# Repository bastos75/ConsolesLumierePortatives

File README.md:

# ConsolesLumierePortatives
Consoles lumière pour spectacle de parade -- connectées par modules MeshBee de Seeedstudio

2 types de console : 
  - la complète avec 4 sorties + telecommande connectable.
  - la réduite avec 1 sortie
  
Les boîtiers sont à imprimer en 3D

Un module de création et de gestion des mémoires lumière est programmé en Processing

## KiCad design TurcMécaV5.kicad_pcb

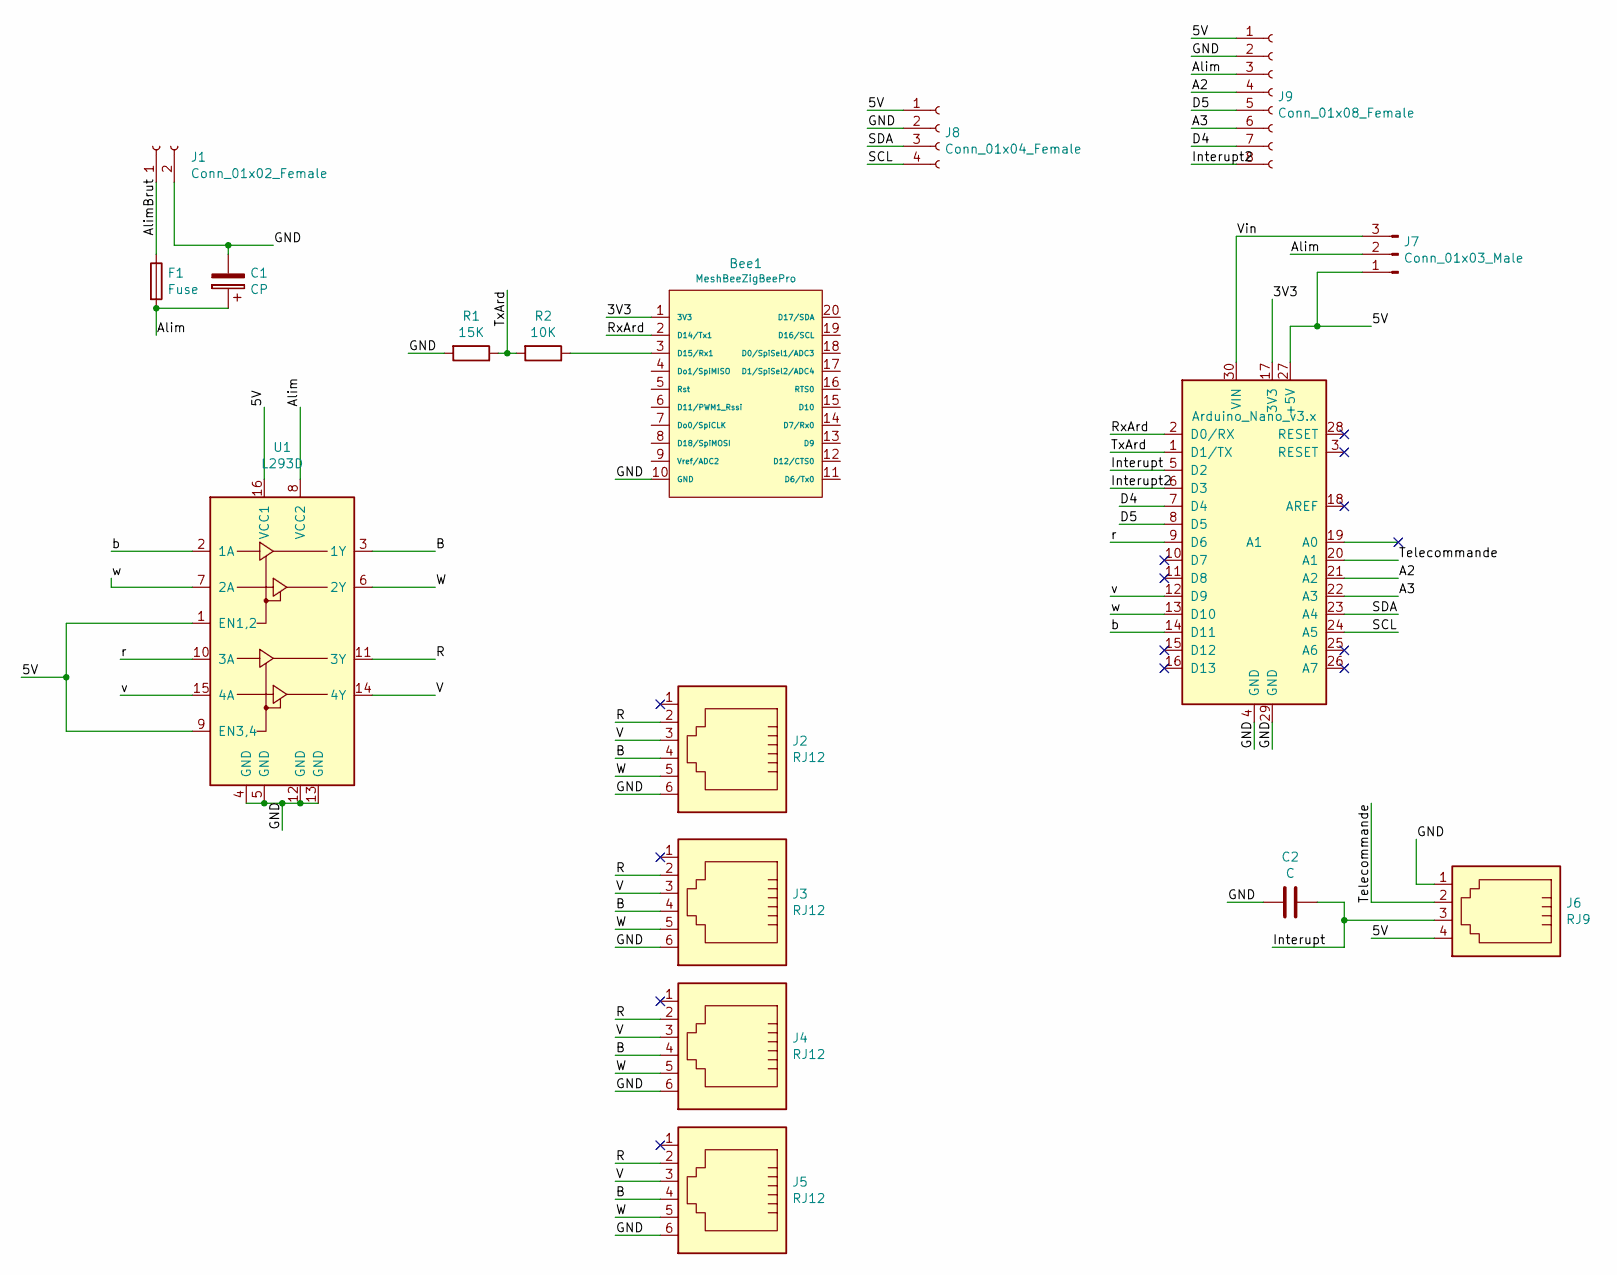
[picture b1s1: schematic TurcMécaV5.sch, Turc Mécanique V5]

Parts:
A1: Arduino_Nano_v3.x; Arduino_NanoPersonnalisé
Bee1: MeshBeeZigBeePro
C1: CP; CP_Radial_D5.0mm_P2.50mm
C2: C; C_Disc_D3.0mm_W1.6mm_P2.50mm
F1: Fuse; Fusible_Fuse_Perso
J1: Conn_01x02_Female; PinHeader_1x02_P2.54mm_Vertical
J2, J3, J4, J5: RJ12; RJ12_Amphenol_54601
J6: RJ9; RJ9_Amphenol_personnalisé
J7: Conn_01x03_Male; FanPinHeader_1x03_P2.54mm_Vertical
J8: Conn_01x04_Female; PinHeader_1x04_P2.54mm_Vertical
J9: Conn_01x08_Female; PinHeader_2x04_P2.54mm_Vertical
R1: 15K; R_Axial_DIN0411_L9.9mm_D3.6mm_P12.70mm_Horizontal
R2: 10K; R_Axial_DIN0411_L9.9mm_D3.6mm_P12.70mm_Horizontal
U1: L293D; DIP-16_W7.62mm_LongPads

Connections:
/3V3: A1.17 (3V3), Bee1.1 (3V3)
/5V: A1.27 (+5V), J6.4, J7.1, J8.1, J9.1, U1.1 (EN1,2), U1.9 (EN3,4), U1.16 (VCC1)
/A2: A1.21 (A2), J9.4
/A3: A1.22 (A3), J9.6
/Alim: C1.1, F1.2, J7.2, J9.3, U1.8 (VCC2)
/AlimBrut: F1.1, J1.1
/B: J2.4, J3.4, J4.4, J5.4, U1.3 (1Y)
/D4: A1.7 (D4), J9.7
/D5: A1.8 (D5), J9.5
/GND: A1.4 (GND), A1.29 (GND), Bee1.10 (GND), C1.2, C2.2, J1.2, J2.6, J3.6, J4.6, J5.6, J6.1, J8.2, J9.2, R1.2, U1.4 (GND), U1.5 (GND), U1.12 (GND), U1.13 (GND)
/Interupt: A1.5 (D2), C2.1, J6.3
/Interupt2: A1.6 (D3), J9.8
/R: J2.2, J3.2, J4.2, J5.2, U1.11 (3Y)
/RxArd: A1.2 (D0/RX), Bee1.2 (D14/Tx1)
/SCL: A1.24 (A5), J8.4
/SDA: A1.23 (A4), J8.3
/Telecommande: A1.20 (A1), J6.2
/TxArd: A1.1 (D1/TX), R1.1, R2.2
/V: J2.3, J3.3, J4.3, J5.3, U1.14 (4Y)
/Vin: A1.30 (VIN), J7.3
/W: J2.5, J3.5, J4.5, J5.5, U1.6 (2Y)
/b: A1.14 (D11), U1.2 (1A)
/r: A1.9 (D6), U1.10 (3A)
/v: A1.12 (D9), U1.15 (4A)
/w: A1.13 (D10), U1.7 (2A)
unnamed: Bee1.3 (D15/Rx1), R2.1

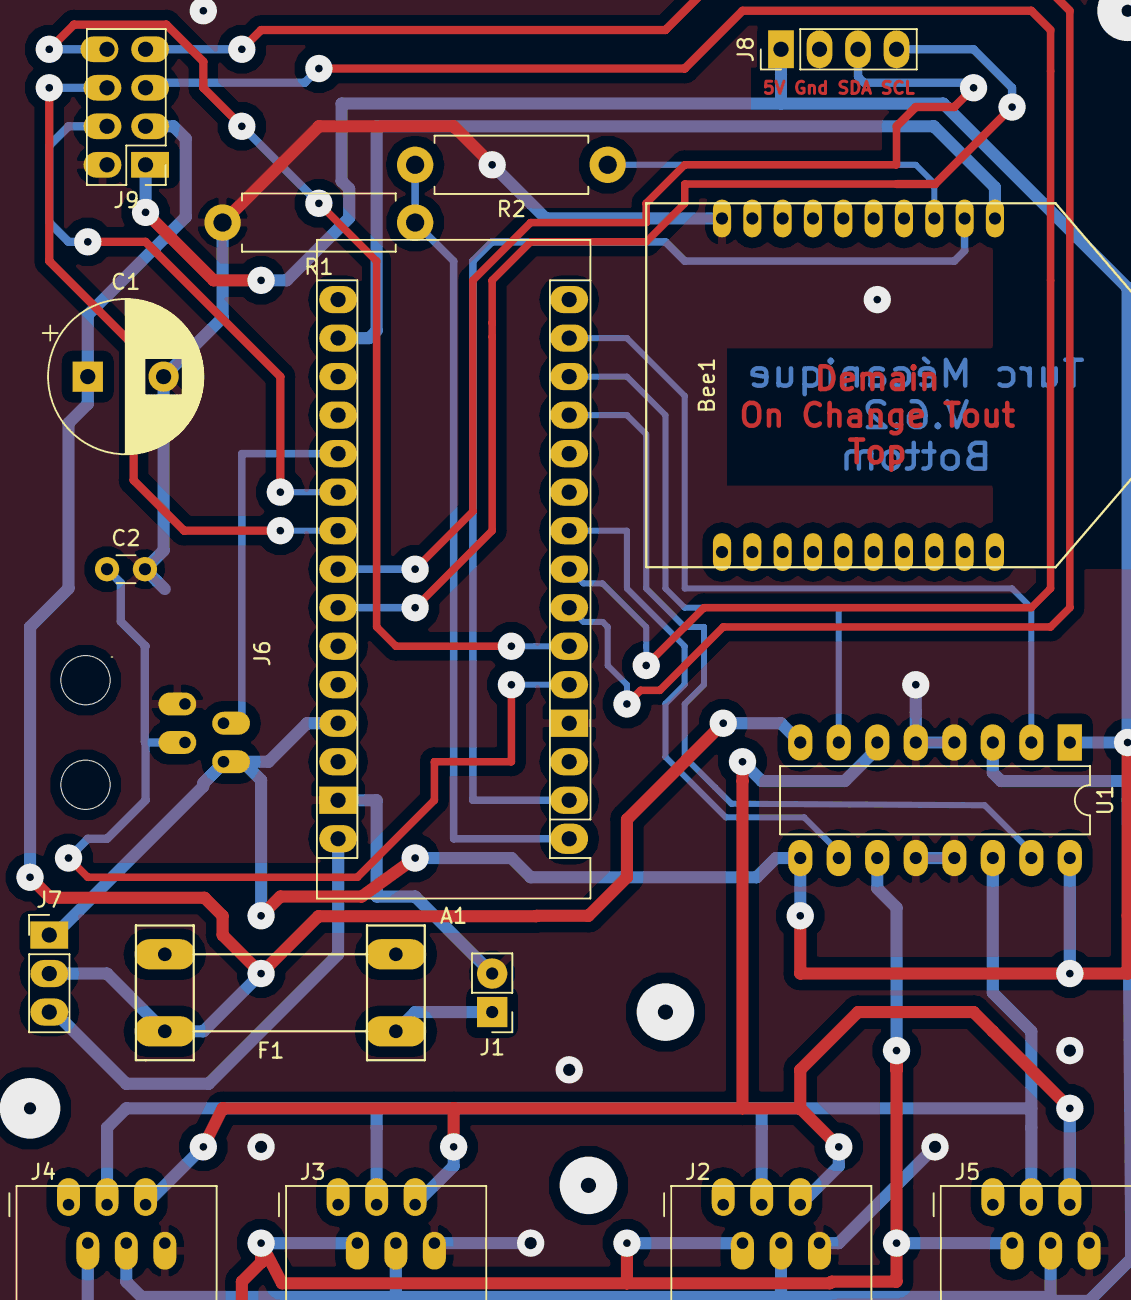
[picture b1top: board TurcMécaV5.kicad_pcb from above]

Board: 2 copper layers, 17 parts (0 on the bottom side), 26 nets.
